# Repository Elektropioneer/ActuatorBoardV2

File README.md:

# ActuatorBoardV2
Actuator board with Arduino Nano. This is the basic version with a ATMEGA328P and support for 6 modules.

Modules include: stepper, relay, DC motor, mosfet versions.

Also included is software, which automatically inits the modules based on the config.

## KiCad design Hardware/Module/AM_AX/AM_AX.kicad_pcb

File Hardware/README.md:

# ActuatorBoardV2
Actuator Board - AT90CAN128

## Software
We are using KiCAD to develop the PCB

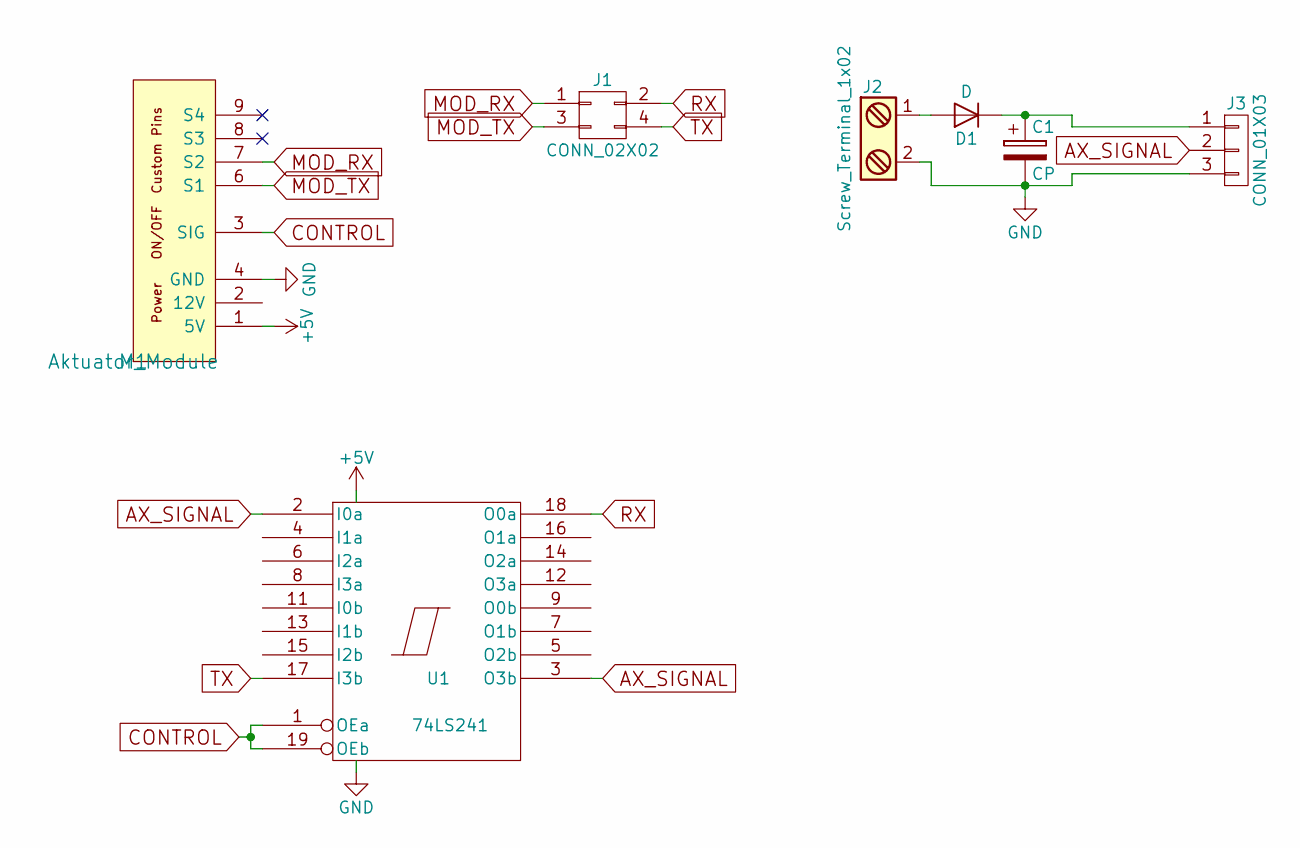
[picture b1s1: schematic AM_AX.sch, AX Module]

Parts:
C1: CP; CP_Elec_5x5.3
D1: D; D_SMB_Standard
J1: CONN_02X02; Pin_Header_Straight_2x02_Pitch2.54mm
J2: Screw_Terminal_1x02; TerminalBlock_Pheonix_MKDS1.5-2pol
J3: CONN_01X03; Pin_Header_Straight_1x03_Pitch2.54mm
M1: Aktuator_Module
U1: 74LS241; DIP-20_W7.62mm

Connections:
+5V: M1.1 (5V), U1.20 (VCC)
AX_SIGNAL: J3.2, U1.2 (I0a), U1.3 (O3b)
CONTROL: M1.3 (SIG), U1.1 (OEa), U1.19 (OEb)
GND: C1.2, J2.2, J3.3, M1.4 (GND), U1.10 (GND)
MOD_RX: J1.1, M1.7 (S2)
MOD_TX: J1.3, M1.6 (S1)
unnamed: C1.1, D1.1 (K), J3.1
unnamed: D1.2 (A), J2.1
RX: J1.2, U1.18 (O0a)
TX: J1.4, U1.17 (I3b)

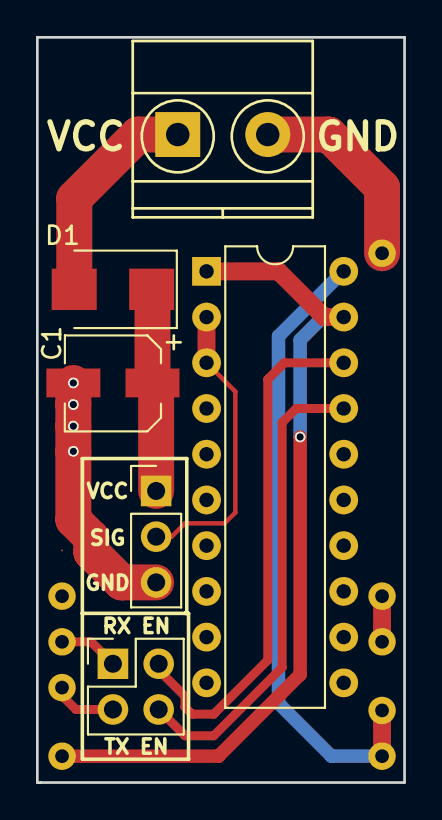
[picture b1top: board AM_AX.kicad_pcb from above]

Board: 2 copper layers, 20.4 x 41.4 mm, 7 parts (0 on the bottom side), 10 nets.

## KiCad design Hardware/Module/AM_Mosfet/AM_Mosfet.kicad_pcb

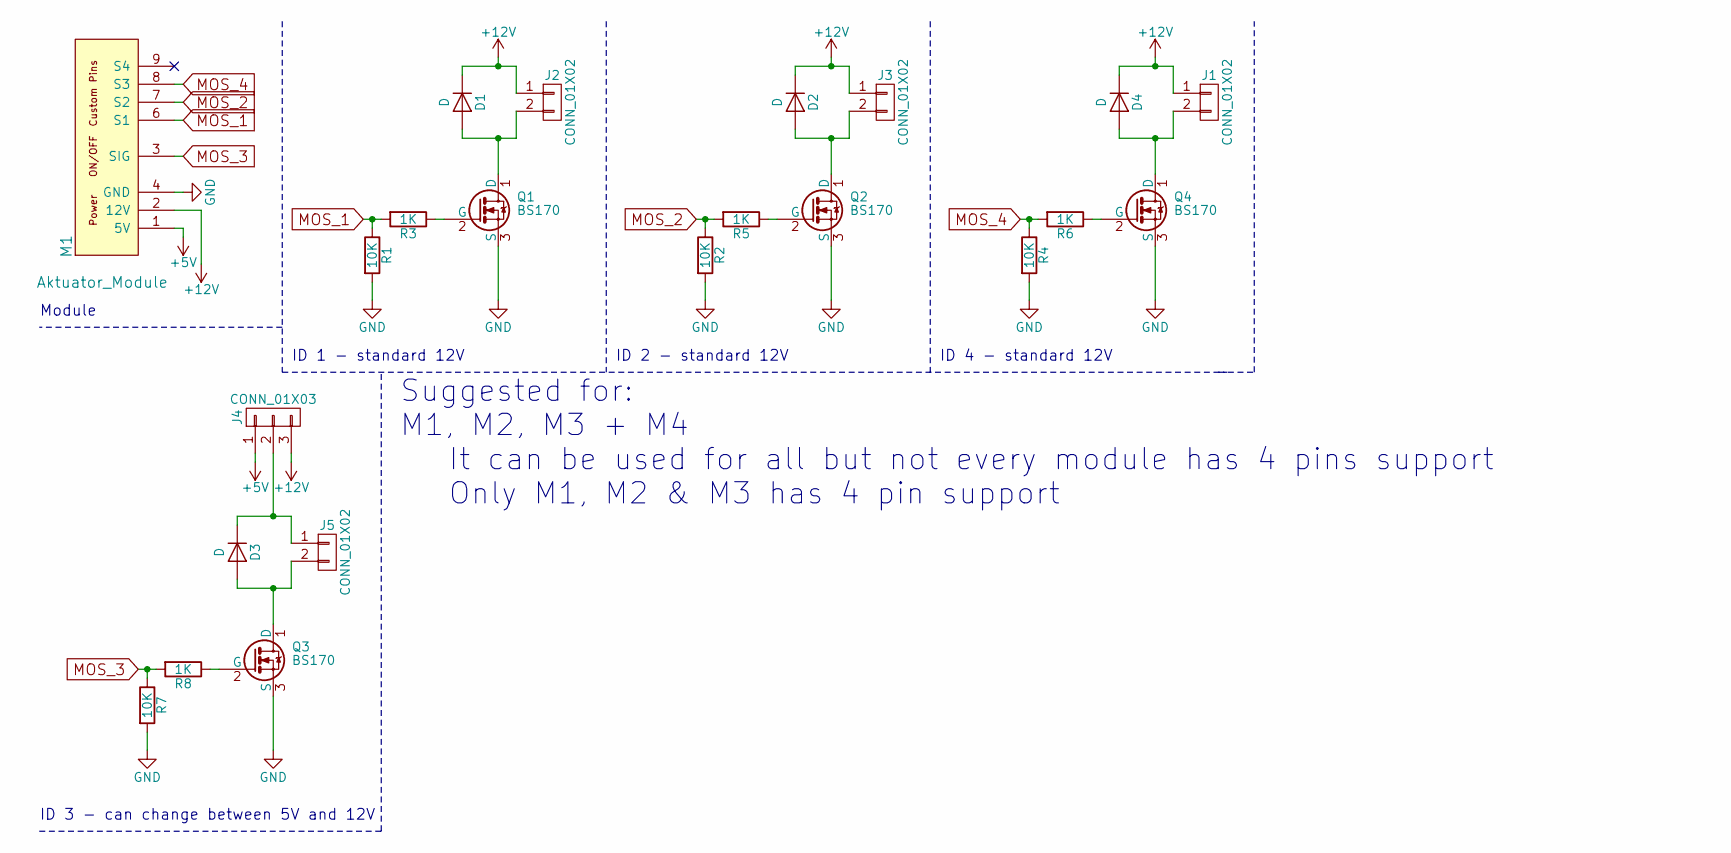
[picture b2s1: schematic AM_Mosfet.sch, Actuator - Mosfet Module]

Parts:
D1, D2, D3, D4: D; D_A-405_P2.54mm_Vertical_AnodeUp
J1, J2, J3, J5: CONN_01X02; Pin_Header_Straight_1x02_Pitch2.54mm
J4: CONN_01X03; Pin_Header_Straight_1x03_Pitch2.54mm
M1: Aktuator_Module
Q1, Q2, Q3, Q4: BS170; TO-92_Inline_Narrow_Oval
R1, R2, R4, R7: 10K; R_0805
R3, R5, R6, R8: 1K; R_0805

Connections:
+5V: J4.1, M1.1 (5V)
+12V: D1.1 (K), D2.1 (K), D4.1 (K), J1.1, J2.1, J3.1, J4.3, M1.2 (12V)
GND: M1.4 (GND), Q1.3 (S), Q2.3 (S), Q3.3 (S), Q4.3 (S), R1.2, R2.2, R4.2, R7.2
MOS_1: M1.6 (S1), R1.1, R3.2
MOS_2: M1.7 (S2), R2.1, R5.2
MOS_3: M1.3 (SIG), R7.1, R8.2
MOS_4: M1.8 (S3), R4.1, R6.2
unnamed: D1.2 (A), J2.2, Q1.1 (D)
unnamed: D2.2 (A), J3.2, Q2.1 (D)
unnamed: D3.1 (K), J4.2, J5.1
unnamed: D3.2 (A), J5.2, Q3.1 (D)
unnamed: D4.2 (A), J1.2, Q4.1 (D)
unnamed: Q1.2 (G), R3.1
unnamed: Q2.2 (G), R5.1
unnamed: Q3.2 (G), R8.1
unnamed: Q4.2 (G), R6.1

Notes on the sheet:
Module
ID 1 - standard 12V
ID 2 - standard 12V
ID 4 - standard 12V
ID 3 - can change between 5V and 12V
Suggested for: M1, M2, M3 + M4 It can be used for all but not every module has 4 pins support Only M1, M2 & M3 has 4 pin support

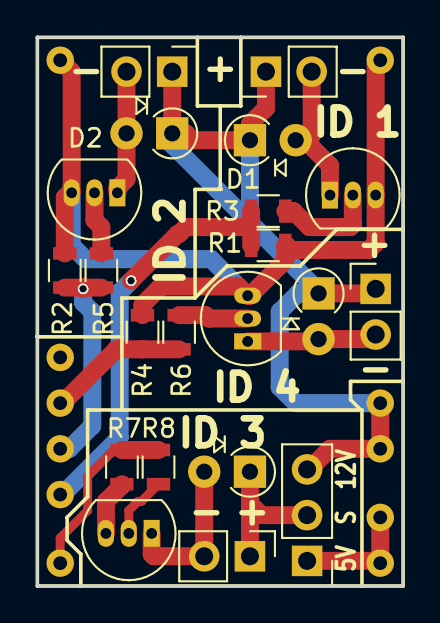
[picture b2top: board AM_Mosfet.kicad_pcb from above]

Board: 2 copper layers, 20.3 x 30.5 mm, 22 parts (0 on the bottom side), 16 nets.

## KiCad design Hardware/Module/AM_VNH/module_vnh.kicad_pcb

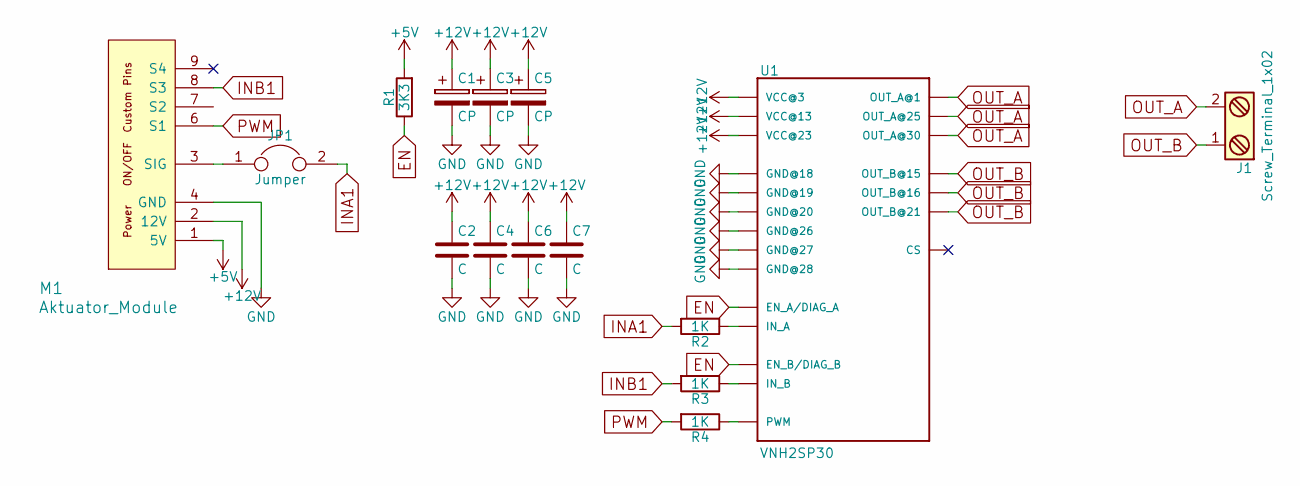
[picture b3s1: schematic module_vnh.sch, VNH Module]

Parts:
C1, C3, C5: CP; CP_Tantalum_Case-U_EIA-6032-15_Reflow
C2, C4, C6, C7: C; C_0805
J1: Screw_Terminal_1x02; TerminalBlock_Pheonix_MKDS1.5-2pol
JP1: Jumper; GS2
M1: Aktuator_Module
R1: 3K3; R_0805
R2, R3, R4: 1K; R_0805
U1: VNH2SP30; MULTIPOWER30

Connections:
+5V: M1.1 (5V), R1.2
+12V: C1.1, C2.1, C3.1, C4.1, C5.1, C6.1, C7.1, M1.2 (12V), U1.P$3 (VCC@3), U1.P$13 (VCC@13), U1.P$23 (VCC@23)
EN: R1.1, U1.P$6 (EN_A/DIAG_A), U1.P$10 (EN_B/DIAG_B)
GND: C1.2, C2.2, C3.2, C4.2, C5.2, C6.2, C7.2, M1.4 (GND), U1.P$18 (GND@18), U1.P$19 (GND@19), U1.P$20 (GND@20), U1.P$26 (GND@26), U1.P$27 (GND@27), U1.P$28 (GND@28)
INA1: JP1.2, R2.2
INB1: M1.8 (S3), R3.2
unnamed: JP1.1, M1.3 (SIG)
unnamed: R2.1, U1.P$5 (IN_A)
unnamed: R3.1, U1.P$11 (IN_B)
unnamed: R4.1, U1.P$8 (PWM)
OUT_A: J1.2, U1.P$1 (OUT_A@1), U1.P$25 (OUT_A@25), U1.P$30 (OUT_A@30)
OUT_B: J1.1, U1.P$15 (OUT_B@15), U1.P$16 (OUT_B@16), U1.P$21 (OUT_B@21)
PWM: M1.6 (S1), R4.2

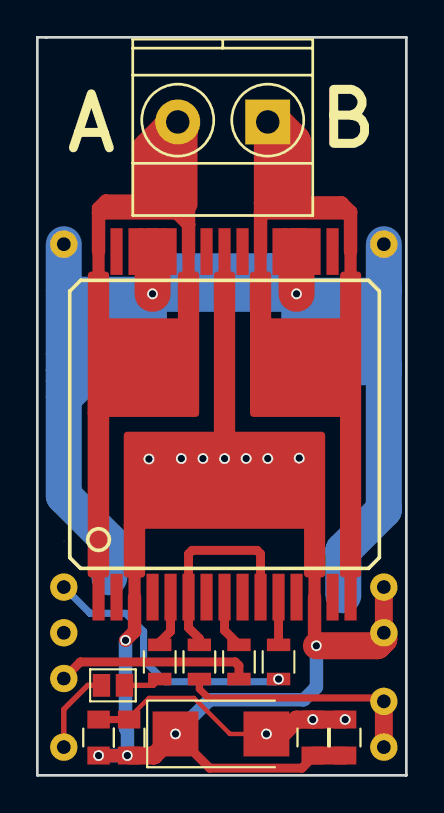
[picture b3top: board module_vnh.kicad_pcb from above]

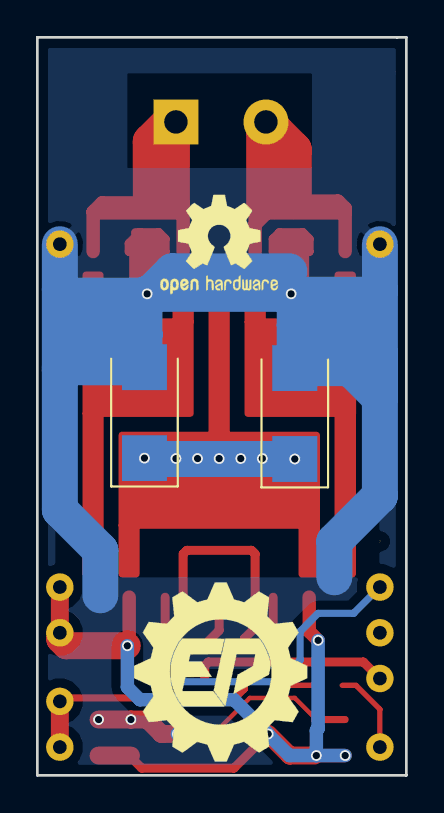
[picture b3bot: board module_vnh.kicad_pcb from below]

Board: 2 copper layers, 20.5 x 41.0 mm, 15 parts (2 on the bottom side), 13 nets.

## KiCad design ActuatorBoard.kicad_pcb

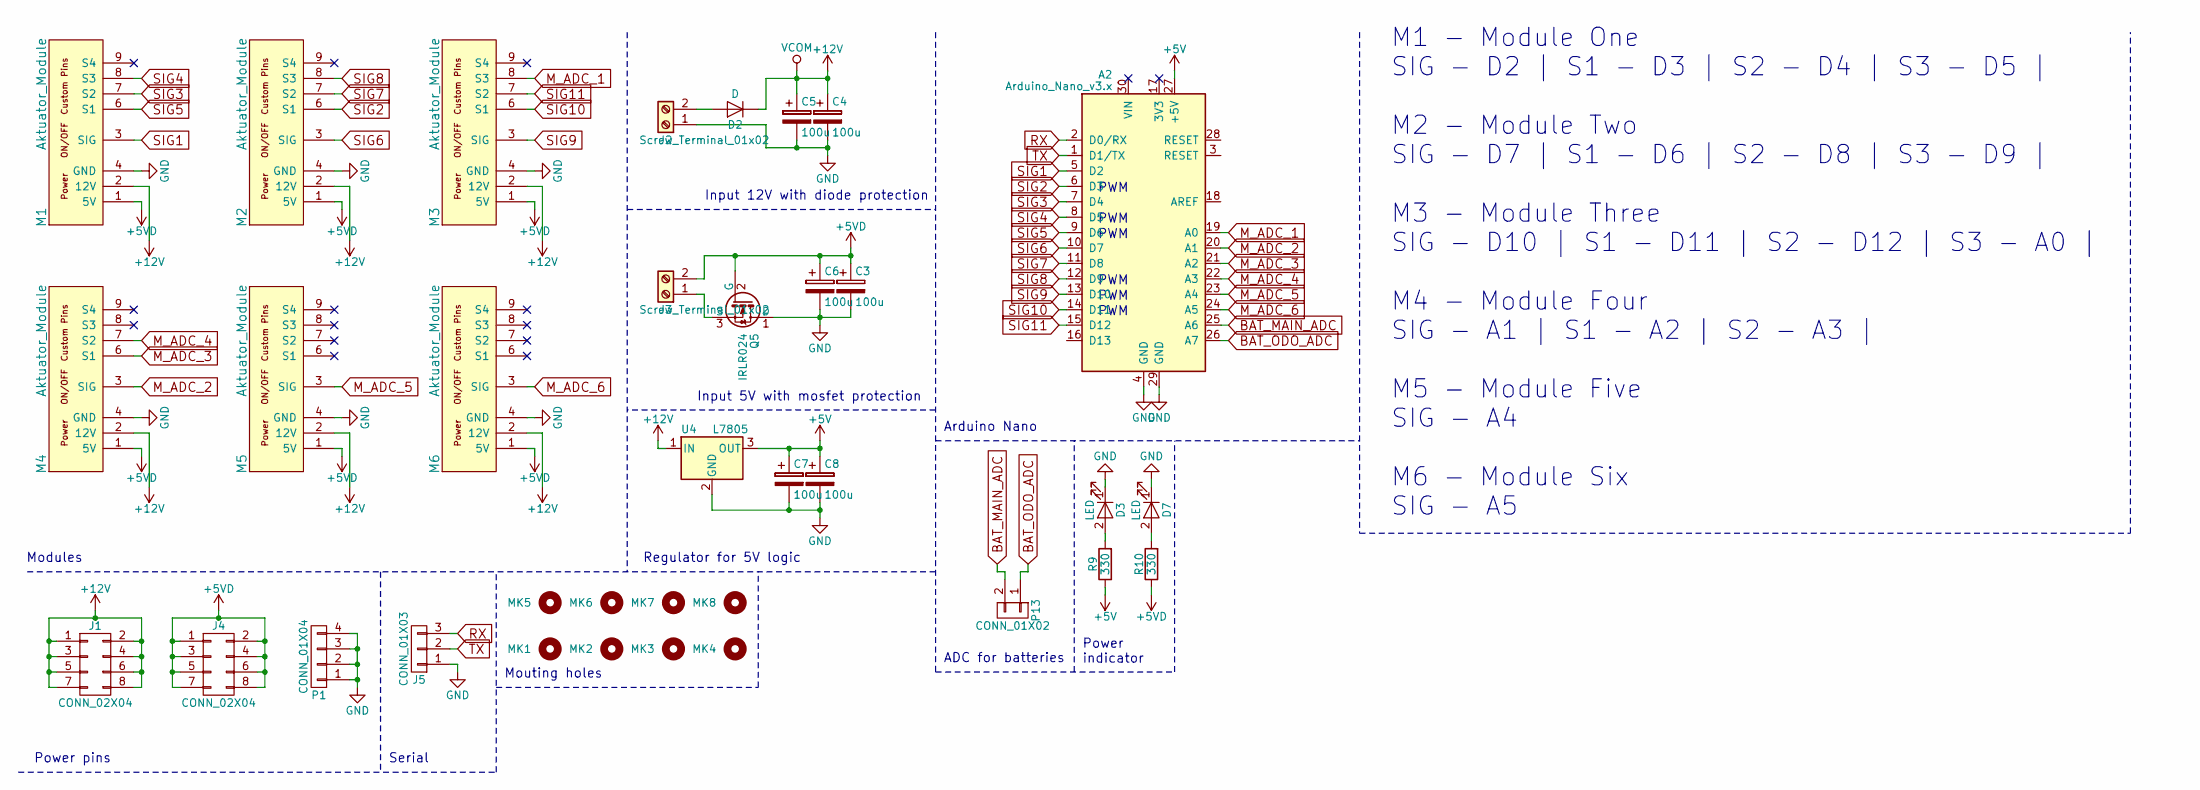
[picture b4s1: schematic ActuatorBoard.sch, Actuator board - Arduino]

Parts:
A2: Arduino_Nano_v3.x; Arduino_Nano_WithMountingHoles
C3, C4, C8: 100u; CP_Elec_6.3x4.5
C5, C6, C7: 100u; CP_Radial_D7.5mm_P2.50mm
D2: D; SMA_Standard
D3, D7: LED; LED_0805
J1, J4: CONN_02X04; Pin_Header_Straight_2x04_Pitch2.54mm
J2, J3: Screw_Terminal_01x02; TerminalBlock_Pheonix_MKDS1.5-2pol
J5: CONN_01X03; Pin_Header_Straight_1x03_Pitch2.54mm
M1, M2, M3, M4, M5, M6: Aktuator_Module
MK1, MK2, MK3, MK4, MK5, MK6, MK7, MK8: Mounting_Hole; MountingHole_3.2mm_M3_Pad_Via
P1: CONN_01X04; Pin_Header_Straight_1x04_Pitch2.54mm
P13: CONN_01X02; Pin_Header_Straight_1x02_Pitch2.54mm
Q5: IRLR024; TO-252-2Lead
R9, R10: 330; R_0805
U4: L7805; TO-252-2Lead

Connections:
+5V: A2.27 (+5V), C7.1, C8.1, R9.1, U4.3 (OUT)
+5VD: C3.1, C6.1, J3.2, J4.1, J4.2, J4.3, J4.4, J4.5, J4.6, J4.7, J4.8, M1.1 (5V), M2.1 (5V), M3.1 (5V), M4.1 (5V), M5.1 (5V), M6.1 (5V), Q5.2 (G), R10.1
+12V: C4.1, C5.1, D2.1 (K), J1.1, J1.2, J1.3, J1.4, J1.5, J1.6, J1.7, J1.8, M1.2 (12V), M2.2 (12V), M3.2 (12V), M4.2 (12V), M5.2 (12V), M6.2 (12V), U4.1 (IN)
BAT_MAIN_ADC: A2.25 (A6), P13.2
BAT_ODO_ADC: A2.26 (A7), P13.1
GND: A2.4 (GND), A2.29 (GND), C3.2, C4.2, C5.2, C6.2, C7.2, C8.2, D3.1 (K), D7.1 (K), J2.1, J5.1, M1.4 (GND), M2.4 (GND), M3.4 (GND), M4.4 (GND), M5.4 (GND), M6.4 (GND), P1.1, P1.2, P1.3, P1.4, Q5.1 (D), U4.2 (GND)
M_ADC_1: A2.19 (A0), M3.8 (S3)
M_ADC_2: A2.20 (A1), M4.3 (SIG)
M_ADC_3: A2.21 (A2), M4.6 (S1)
M_ADC_4: A2.22 (A3), M4.7 (S2)
M_ADC_5: A2.23 (A4), M5.3 (SIG)
M_ADC_6: A2.24 (A5), M6.3 (SIG)
unnamed: D2.2 (A), J2.2
unnamed: D3.2 (A), R9.2
unnamed: D7.2 (A), R10.2
unnamed: J3.1, Q5.3 (S)
RX: A2.2 (D0/RX), J5.3
SIG1: A2.5 (D2), M1.3 (SIG)
SIG2: A2.6 (D3), M2.6 (S1)
SIG3: A2.7 (D4), M1.7 (S2)
SIG4: A2.8 (D5), M1.8 (S3)
SIG5: A2.9 (D6), M1.6 (S1)
SIG6: A2.10 (D7), M2.3 (SIG)
SIG7: A2.11 (D8), M2.7 (S2)
SIG8: A2.12 (D9), M2.8 (S3)
SIG9: A2.13 (D10), M3.3 (SIG)
SIG10: A2.14 (D11), M3.6 (S1)
SIG11: A2.15 (D12), M3.7 (S2)
TX: A2.1 (D1/TX), J5.2

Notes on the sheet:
Input 12V with diode protection
Input 5V with mosfet protection
Regulator for 5V logic
PWM
Modules
Power pins
Serial
Mouting holes
ADC for batteries
Power indicator
Arduino Nano
M1 - Module One SIG - D2 | S1 - D3 | S2 - D4 | S3 - D5 | M2 - Module Two SIG - D7 | S1 - D6 | S2 - D8 | S3 - D9 | M3 - Module Three SIG - D10 | S1 - D11 | S2 - D12 | S3 - A0 | M4 - Module Four SIG - A1 | S1 - A2 | S2 - A3 | M5 - Module Five SIG - A4 M6 - Module Six SIG - A5

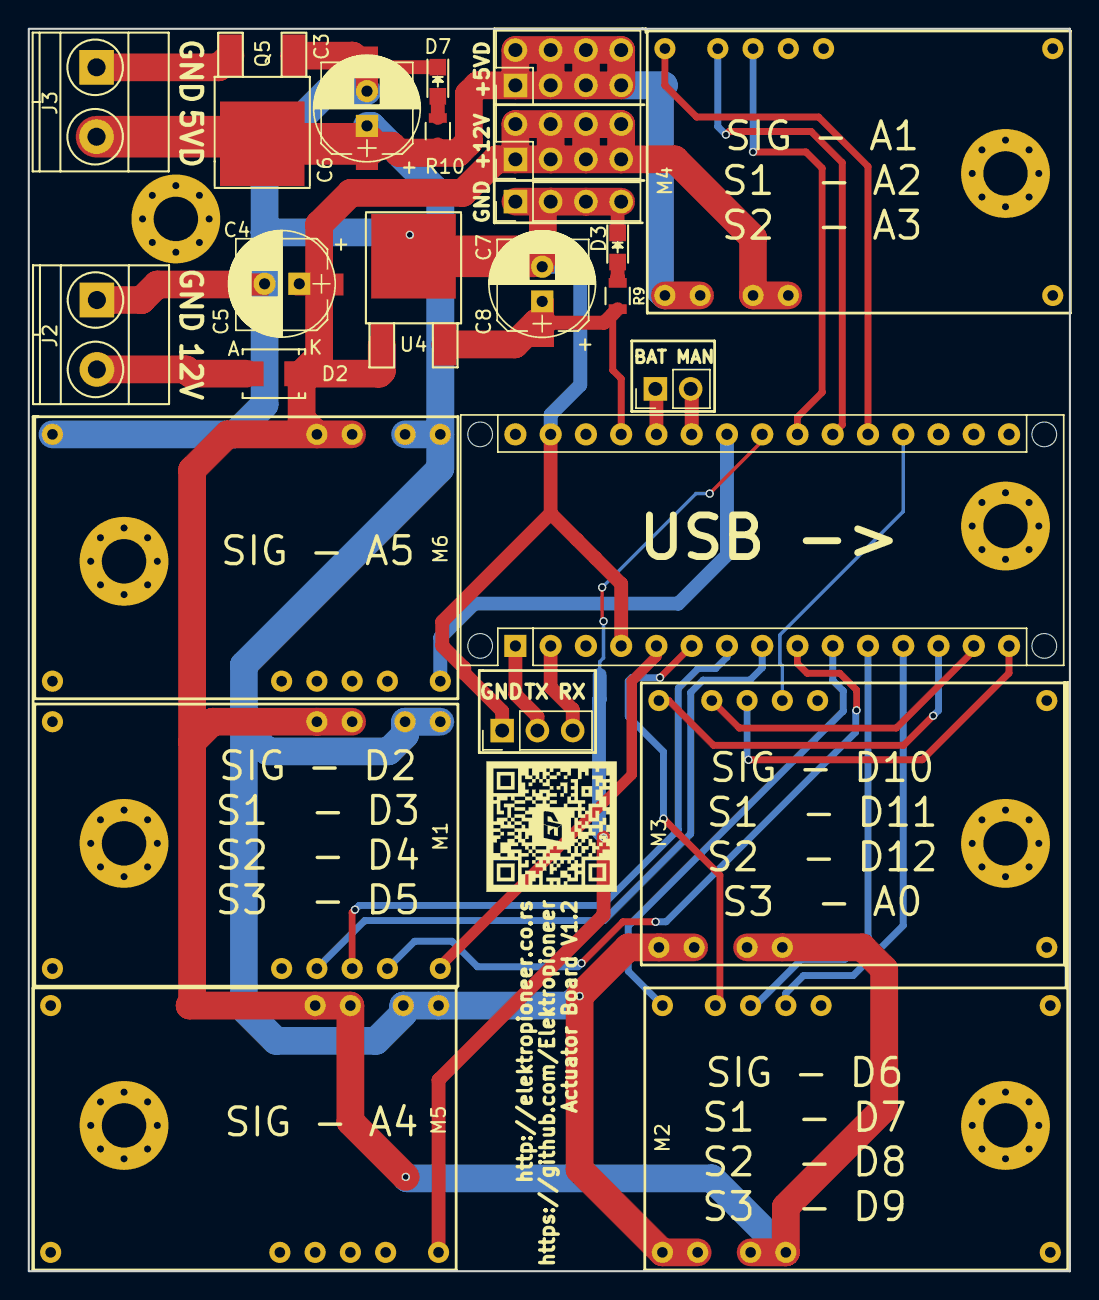
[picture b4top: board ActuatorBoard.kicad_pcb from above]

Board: 2 copper layers, 75.0 x 89.5 mm, 35 parts (0 on the bottom side), 29 nets.

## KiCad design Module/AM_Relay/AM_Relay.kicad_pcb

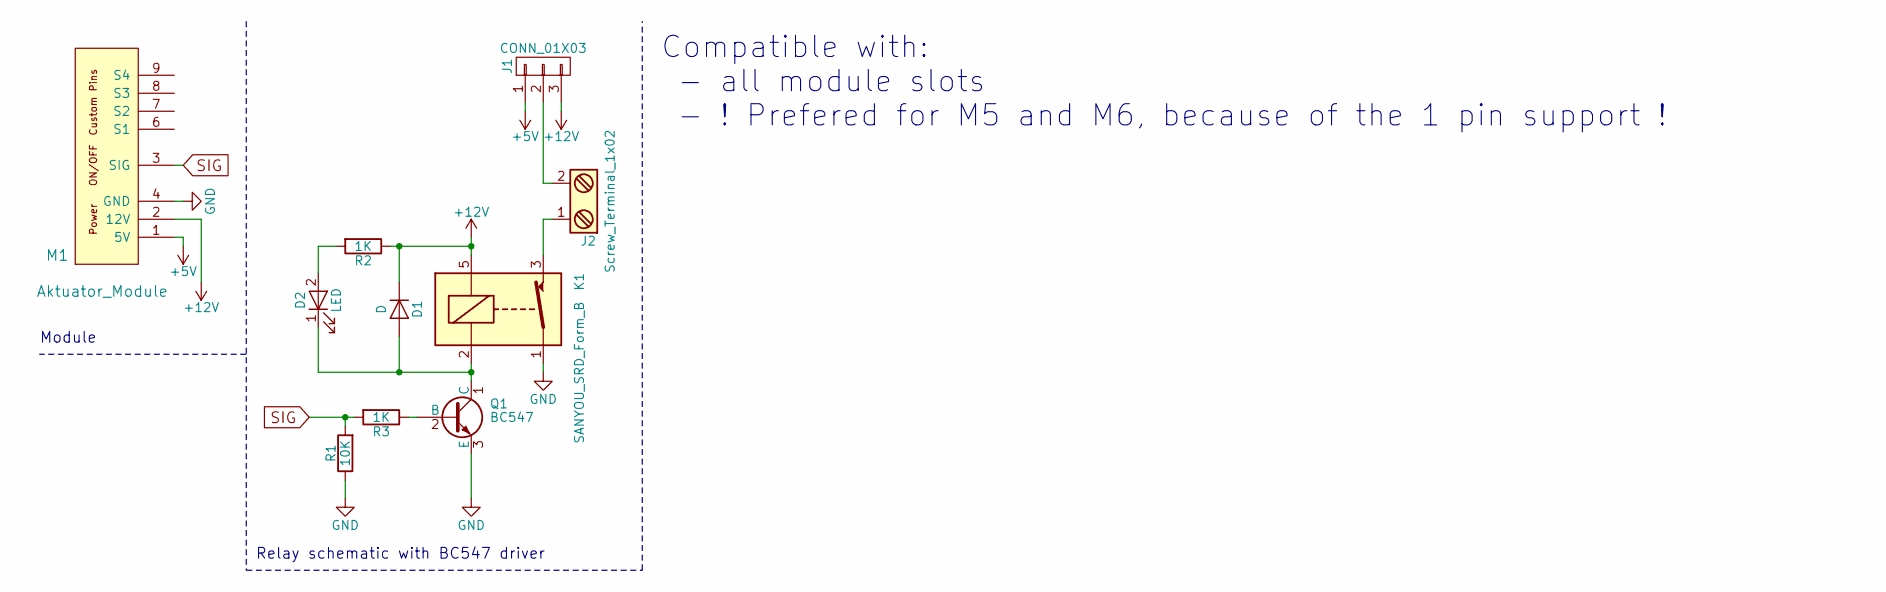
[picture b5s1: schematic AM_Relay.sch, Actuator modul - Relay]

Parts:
D1: D; D_A-405_P2.54mm_Vertical_AnodeUp
D2: LED; LED_0805
J1: CONN_01X03; Pin_Header_Straight_1x03_Pitch2.54mm
J2: Screw_Terminal_1x02; TerminalBlock_Pheonix_MKDS1.5-2pol
K1: SANYOU_SRD_Form_B; Relay_SANYOU_SRD_Series_Form_C
M1: Aktuator_Module
Q1: BC547; TO-92_Inline_Narrow_Oval
R1: 10K; R_0805
R2, R3: 1K; R_0805

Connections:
+5V: J1.1, M1.1 (5V)
+12V: D1.1 (K), J1.3, K1.5, M1.2 (12V), R2.1
GND: K1.1, M1.4 (GND), Q1.3 (E), R1.1
unnamed: D1.2 (A), D2.1 (K), K1.2, Q1.1 (C)
unnamed: D2.2 (A), R2.2
unnamed: J1.2, J2.2
unnamed: J2.1, K1.3
unnamed: Q1.2 (B), R3.1
SIG: M1.3 (SIG), R1.2, R3.2

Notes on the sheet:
Module
Relay schematic with BC547 driver
Compatible with: - all module slots - ! Prefered for M5 and M6, because of the 1 pin support !

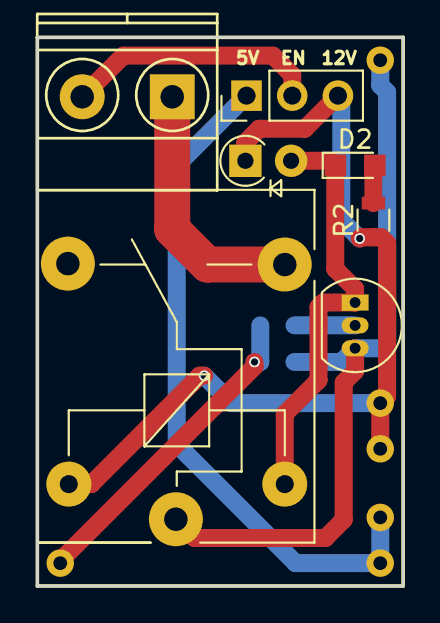
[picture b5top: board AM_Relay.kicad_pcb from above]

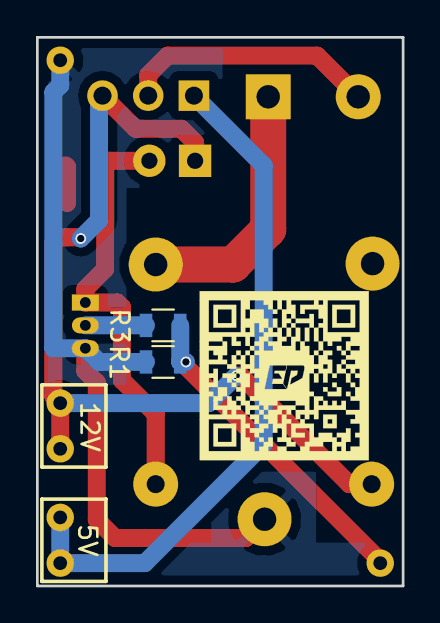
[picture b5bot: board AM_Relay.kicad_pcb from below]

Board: 2 copper layers, 20.3 x 30.5 mm, 10 parts (2 on the bottom side), 9 nets.

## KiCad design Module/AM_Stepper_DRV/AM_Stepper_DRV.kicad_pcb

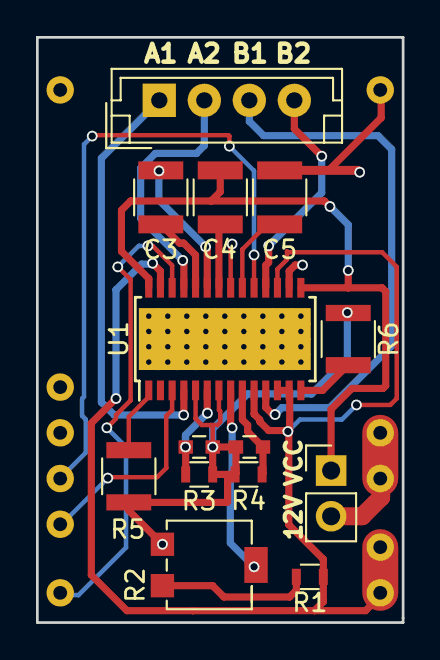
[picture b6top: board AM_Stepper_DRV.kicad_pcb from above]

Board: 2 copper layers, 20.3 x 32.5 mm, 15 parts (0 on the bottom side), 21 nets.

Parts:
C1, C2: 220p; C_0603
C3, C4, C5: 220n; C_1210
J1: CONN_01X04; JST_EH_B04B-EH-A_04x2.50mm_Straight
J2: CONN_01X02; Pin_Header_Straight_1x02_Pitch2.54mm
M1: Aktuator_Module
R1: 3K9; R_0603
R2: TRIMPOTSMD; Potentiometer_Trimmer_Bourns_3214G
R3, R4: 220k; R_0603
R5, R6: 0r22; R_1210
U1: DRV8811; HTSSOP-28_4.4x9.7mm_Pitch0.65mm_ThermalPad

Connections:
5V: M1.1, R1.2, U1.10, U1.12, U1.13, U1.17, U1.27
DIR: M1.6, U1.3
EN: M1.3, U1.26
GND: C1.2, C2.2, C5.2, M1.4, R2.3, R3.2, R4.2, R5.1, R6.1, U1.5, U1.7, U1.16, U1.21
unnamed: C1.1, R3.1, U1.6
unnamed: C2.1, R4.1, U1.9
unnamed: C3.1, U1.23
unnamed: C3.2, U1.24
unnamed: C4.1, U1.22
unnamed: C5.1, U1.20
unnamed: J1.1, U1.4
unnamed: J1.2, U1.25
unnamed: J1.3, U1.11
unnamed: J1.4, U1.18
unnamed: J2.2, M1.2
unnamed: R1.1, R2.1
unnamed: R2.2, U1.8
unnamed: R5.2, U1.1
unnamed: R6.2, U1.14
STEP: M1.7, U1.19
VCC: C4.2, J2.1, U1.15, U1.28

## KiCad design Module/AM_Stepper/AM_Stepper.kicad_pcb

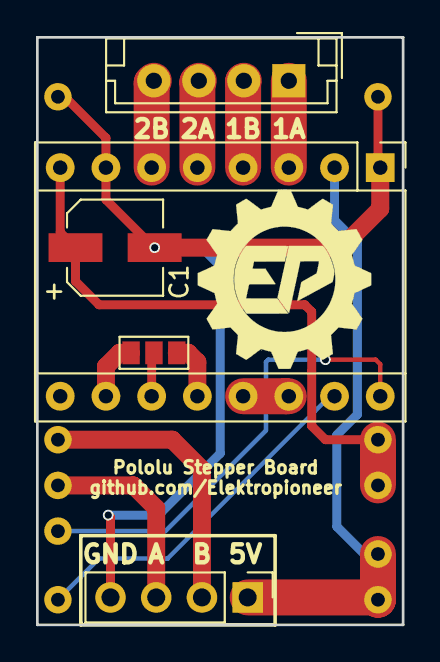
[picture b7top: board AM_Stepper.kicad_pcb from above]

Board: 2 copper layers, 20.3 x 32.6 mm, 6 parts (0 on the bottom side), 15 nets.

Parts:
A1: Pololu_Breakout_A4988; Pololu_Breakout-16_15.2x20.3mm
C1: CP; CP_Elec_5x4.5
J1: CONN_01X04; JST_EH_B04B-EH-A_04x2.50mm_Straight
J2: CONN_01X04; Pin_Header_Straight_1x04_Pitch2.54mm
J3: CONN_01X03; GS3
M1: Aktuator_Module

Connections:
+5V: A1.2, J2.1, M1.1
+12V: A1.8, C1.1, M1.2
DIRECTION: A1.16, M1.6
ENC_A: J2.3, M1.7
ENC_B: J2.2, M1.8
GND: A1.1, A1.7, C1.2, J2.4, M1.4
unnamed: A1.3, J1.1
unnamed: A1.4, J1.2
unnamed: A1.5, J1.3
unnamed: A1.6, J1.4
unnamed: A1.10, J3.3
unnamed: A1.11, J3.2
unnamed: A1.12, J3.1
unnamed: A1.13, A1.14
STEP: A1.15, M1.3

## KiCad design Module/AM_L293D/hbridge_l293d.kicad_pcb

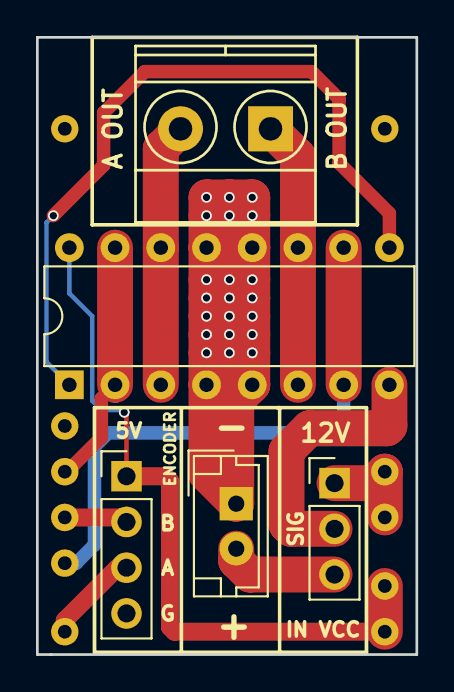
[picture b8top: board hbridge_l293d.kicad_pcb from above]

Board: 2 copper layers, 21.1 x 34.3 mm, 6 parts (0 on the bottom side), 12 nets.

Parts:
J1: CONN_01X03; Pin_Header_Straight_1x03_Pitch2.54mm
J2: Screw_Terminal_1x02; JST_EH_B02B-EH-A_02x2.50mm_Straight
J3: Screw_Terminal_1x02; TerminalBlock_Pheonix_MKDS1.5-2pol
J4: CONN_01X04; Pin_Header_Straight_1x04_Pitch2.54mm
M1: Aktuator_Module
U1: L293D; DIP-16_W7.62mm

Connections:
5V: J4.1, M1.1, U1.16
12V: J1.1, M1.2
A_ENC: J4.3, M1.3
A_OUT: J3.2, U1.3, U1.14
A_PWM: M1.8, U1.2, U1.15
B_ENC: J4.2, M1.7
B_OUT: J3.1, U1.6, U1.11
B_PWM: M1.6, U1.7, U1.10
GND: J2.1, J4.4, M1.4, U1.4, U1.5, U1.12, U1.13
IN_VCC: J1.3, J2.2
unnamed: U1.1, U1.9
VCC: J1.2, U1.8

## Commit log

2017-11-01 Added main files...
2017-11-06 Added output files
2017-11-06 Added .cad
2017-11-06 Added images
2017-11-06 Added pdf
2017-11-06 Changed the schematic to look more fancy (pdf update)
2017-11-07 Added new pdf, added tx rx debug pins
2017-11-08 Added new wrl files, and did repairs
2017-11-08 Added cad file
2017-11-08 Added new stuff
2017-11-09 Moved files
2017-11-16 12V relays...
2017-11-16 12V...
2017-11-16 save...
2018-02-10 Actuator board with modules
2018-02-10 Added outputs, pdf, screenshots
2018-02-14 Extending the stepper and redesigning
2018-02-18 Changed position of two pins because of future h bridge pwm requirements
2018-02-26 Added actuator board drill and gerber
2018-02-26 Added l293d module gerber files
2018-02-26 Added mosfet module gerber
2018-02-26 Relay gerber files
2018-02-26 Stepper driver gerber
2018-02-26 Added drv gerber
2018-03-26 Moving to hardware folder and software. Added software which is in beta
2018-03-26 Added readme
2018-04-03 Comments and direct l293d support
2018-04-03 A bit of changes
2018-04-05 Testing for VNH modules
2018-04-09 added the Ax Module
2018-04-16 added second stepper support
2018-04-16 Modif to new stepper module
2018-04-16 Changes some files for the stepper
